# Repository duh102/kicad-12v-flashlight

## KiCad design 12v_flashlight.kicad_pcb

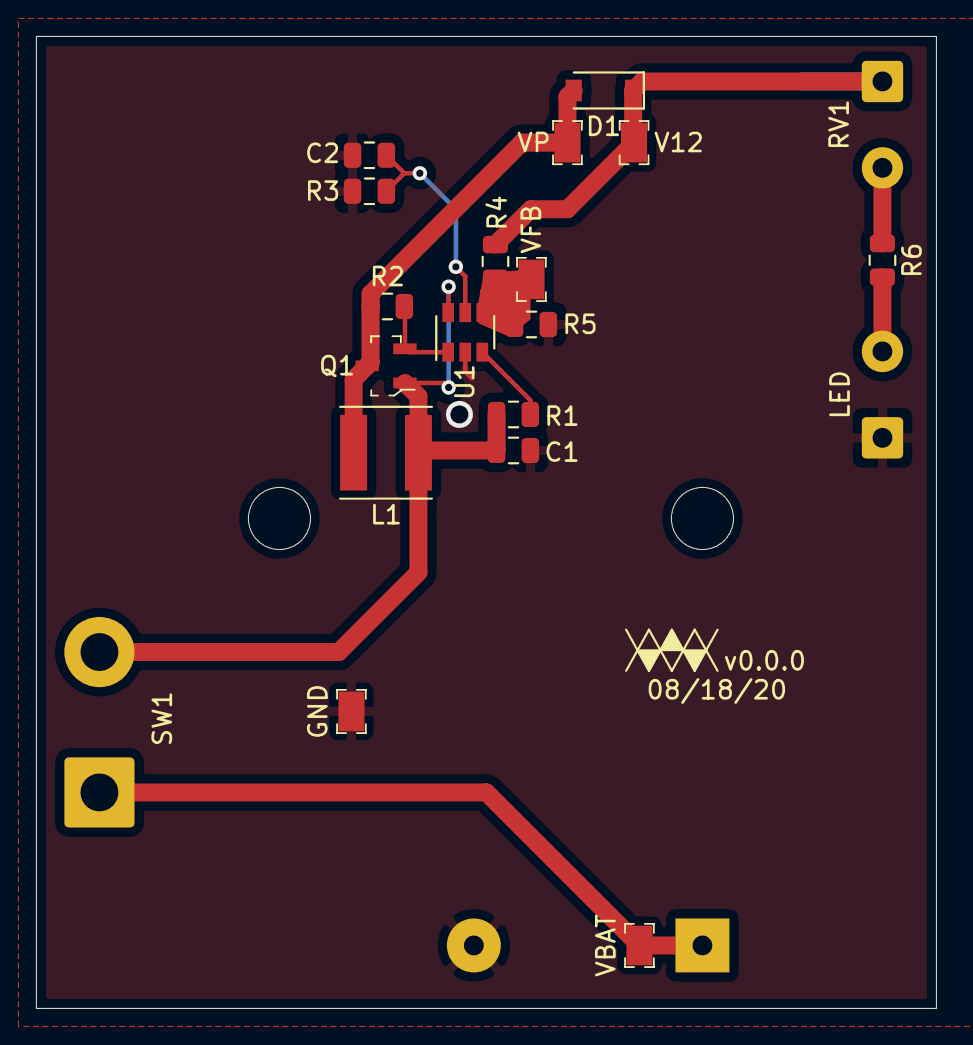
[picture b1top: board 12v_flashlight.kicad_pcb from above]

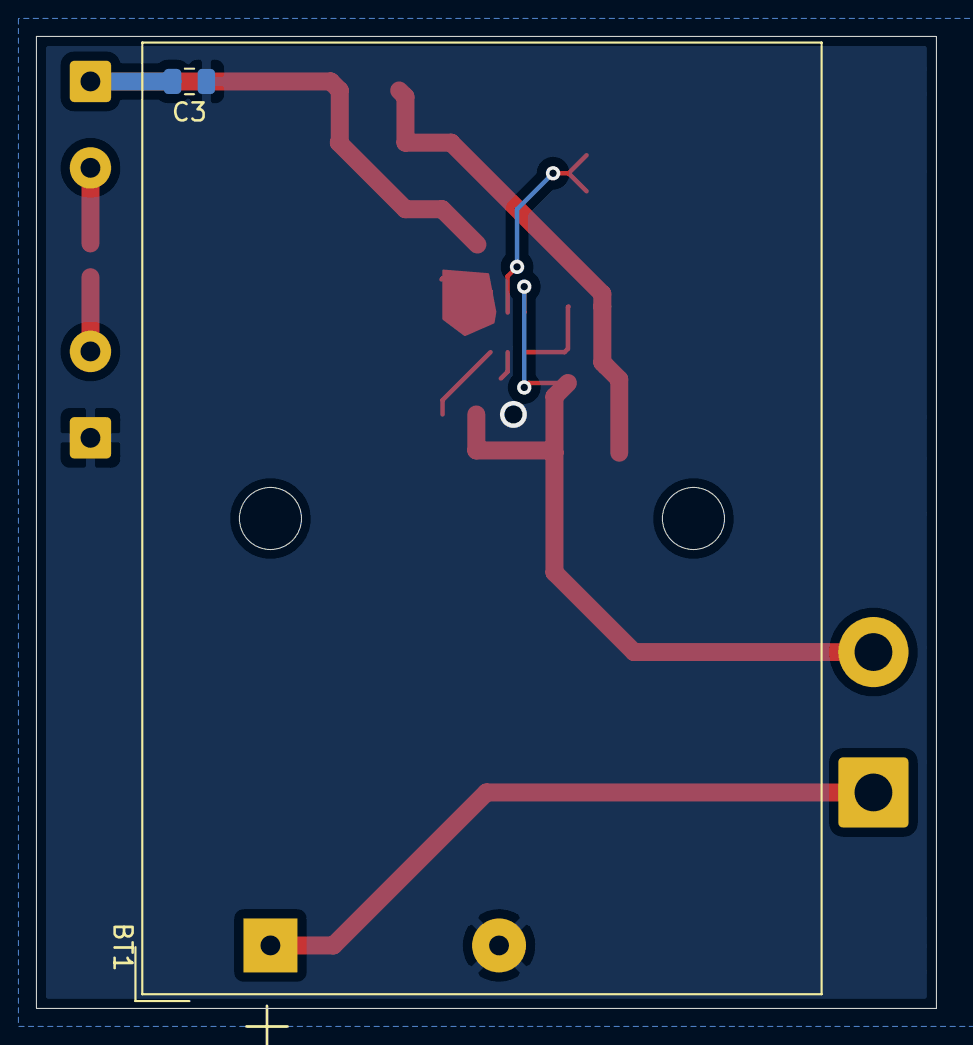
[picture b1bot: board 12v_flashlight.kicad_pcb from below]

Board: 2 copper layers, 50.0 x 54.0 mm, 22 parts (2 on the bottom side), 11 nets.

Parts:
BT1: Battery; BatteryHolder_Keystone_2479_3xAAA
C1, C3: 10uF; C_0805_2012Metric
C2: 2.2uF; C_0805_2012Metric
D1: D_Schottky; D_SOD-123
GND: RCT-0C; PROBE_PAD_0805
L1: INDUCTOR; L_Taiyo-Yuden_NR-50xx
LED: LED_Series; SolderWire-0.5sqmm_1x02_P4.8mm_D0.9mm_OD2.3mm
Q1: BSS138; SOT-23-3
R1: 10kR; R_0805_2012Metric
R2: 300R; R_0805_2012Metric
R3: 2kR; R_0805_2012Metric
R4: 1M6R; R_0805_2012Metric
R5: 180kR; R_0805_2012Metric
R6: 10R; R_0805_2012Metric
RV1: R_POT; SolderWire-0.5sqmm_1x02_P4.8mm_D0.9mm_OD2.3mm
SW1: SW_SPST; SolderWire-1.5sqmm_1x02_P7.8mm_D1.7mm_OD3.9mm
U1: MCP1640CH; SOT-23-6
V12: RCT-0C; PROBE_PAD_0805
VBAT: RCT-0C; PROBE_PAD_0805
VFB: RCT-0C; PROBE_PAD_0805
VP: RCT-0C; PROBE_PAD_0805

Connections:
12V: C3.1, D1.1, R4.1, RV1.1, V12.1
FB: R4.2, R5.1, U1.4, VFB.1
GND: BT1.2, C1.2, C2.2, C3.2, GND.1, LED.1, R3.2, R5.2, U1.2
unnamed: BT1.1, SW1.1, VBAT.1
unnamed: C2.1, R3.1, U1.5
unnamed: D1.2, L1.2, Q1.3, R2.1, VP.1
unnamed: LED.2, R6.2
unnamed: Q1.2, R2.2, U1.1
unnamed: R1.2, U1.3
unnamed: R6.1, RV1.2
VIN: C1.1, L1.1, Q1.1, R1.1, SW1.2, U1.6

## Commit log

2020-12-09 Initial commit; never tracked it
